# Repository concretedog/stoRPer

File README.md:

# 

stoRPer, a modular adaptable AWD Pico based robot rover

[Check out the youtube video](https://youtu.be/Y8ddx1Og3Xw?feature=shared) with details about the design and the design thinking, at the moment it's probably the best documentation! 

Basic Bill Of Materials, This is just a guide for a basic build as you could build up the PCB in any way you can imagine!

- The PCB, Available on [Tindie](https://www.tindie.com/products/concreted0g/storper/)
- 4* N20 metal gear motors in a gear ratio of your choice rated up to 6V. <br />
- 4* 3D printed motor mount clips to attach the motors (files in the 3D models section or periodically available on the tindie listing as an options)<br />
- 8* 6mm M2 bolts and nuts to attach motor mounts.<br />
- A raspberry pi Pico or Pico W, or equivalent footprint microcontroller board.<br />
- Some N20 compatible wheels (either commercial or home brew/3D printed)<br />
- Some kind of power supply (simplest is a small USB pack, other options are a 14500 or 18650 cell wired into the power input)<br />
- Semi optional, an upper deck to attach power supply too. (Inkscape files for Lasercutting or CNC or heck, cutting out with a saw, are in the Deck Drawing folder, or available lasercut on the Tindie listing)<br />

But that's just a guide, you could use different items or design to the basic PCB/chassis in different ways. <br />

All the KiCad files in the repo were originally made in version 7.xx. 

**Update 28-05-2024**

Added an Addons folder which currently contains 2 new PCB designs. <br />

Bumper can receive an ultrasonic module (HC-SR04) and also have 2 bump switches connected. <br />
The Kludge Deck conforms to the StoRPer main PCB layout with lots of prototyping space and extra holes for mounting stuff! <br />

Bumpers can be added above or below the main PCB with lots of different mount options. Therefore you might need to buy a range of standoffs to accomodate and support your design. If however you have access to a 3D printer there is a FreeCAD file in the 3D models section called STANDOFFS which you can simply adjust the length of a standoff tube that will slot over an M3 bolt. You can make custom lengths to suit your build. 

**Tiny Update 29-06-25**

Added a small hex adaptor part to the 3D models section. I ran a workshop recently and wanted to use more affordable mecanum wheels and found some cheap 48mm mecanum wheels available on places like aliexpress etc. However they have a hexagonal axle mount. After numerous iterations and dialling in the 3D printing I made a super simple slip on adaptor part that sits inside the wheel and slots on snugly to the N20 motor mount. Useful for stoRPer of course, but useful for any N20 motor project.

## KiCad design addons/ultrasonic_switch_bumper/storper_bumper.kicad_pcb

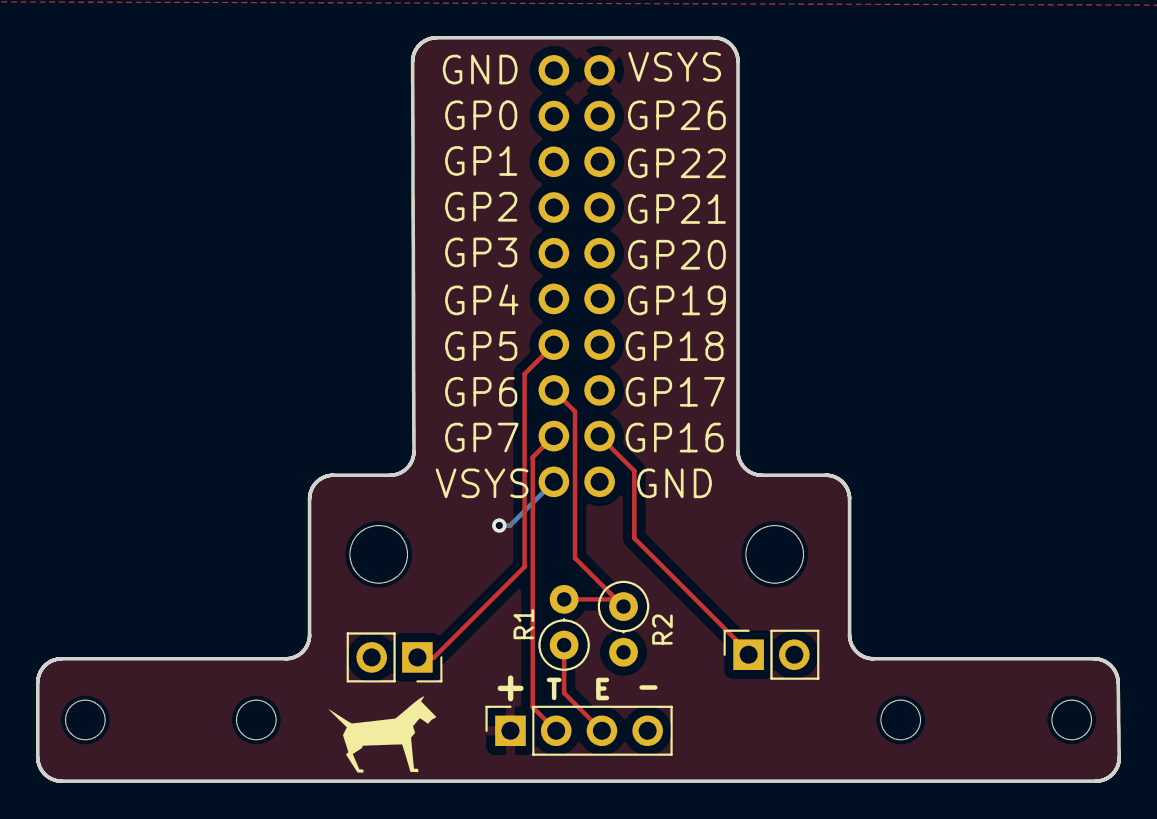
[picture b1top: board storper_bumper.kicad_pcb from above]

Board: 2 copper layers, 60.1 x 41.3 mm, 6 parts (0 on the bottom side), 7 nets.

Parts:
J1: HRS04; PinSocket_1x04_P2.54mm_Vertical
J2, J3: Conn_01x02_Pin; PinSocket_1x02_P2.54mm_Vertical
J12: Conn_02x10_Counter_Clockwise; stoRPer_breakout
R1, R2: R; R_Axial_DIN0207_L6.3mm_D2.5mm_P2.54mm_Vertical

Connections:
/gp5: J2.1, J12.7
/gp6: J12.8, R1.2, R2.1
/gp7: J1.2, J12.9
/gp16: J3.1, J12.12
GND: J1.4, J2.2, J3.2, J12.1, J12.11, R2.2
unnamed: J1.3, R1.1
VSS: J1.1, J12.10, J12.20

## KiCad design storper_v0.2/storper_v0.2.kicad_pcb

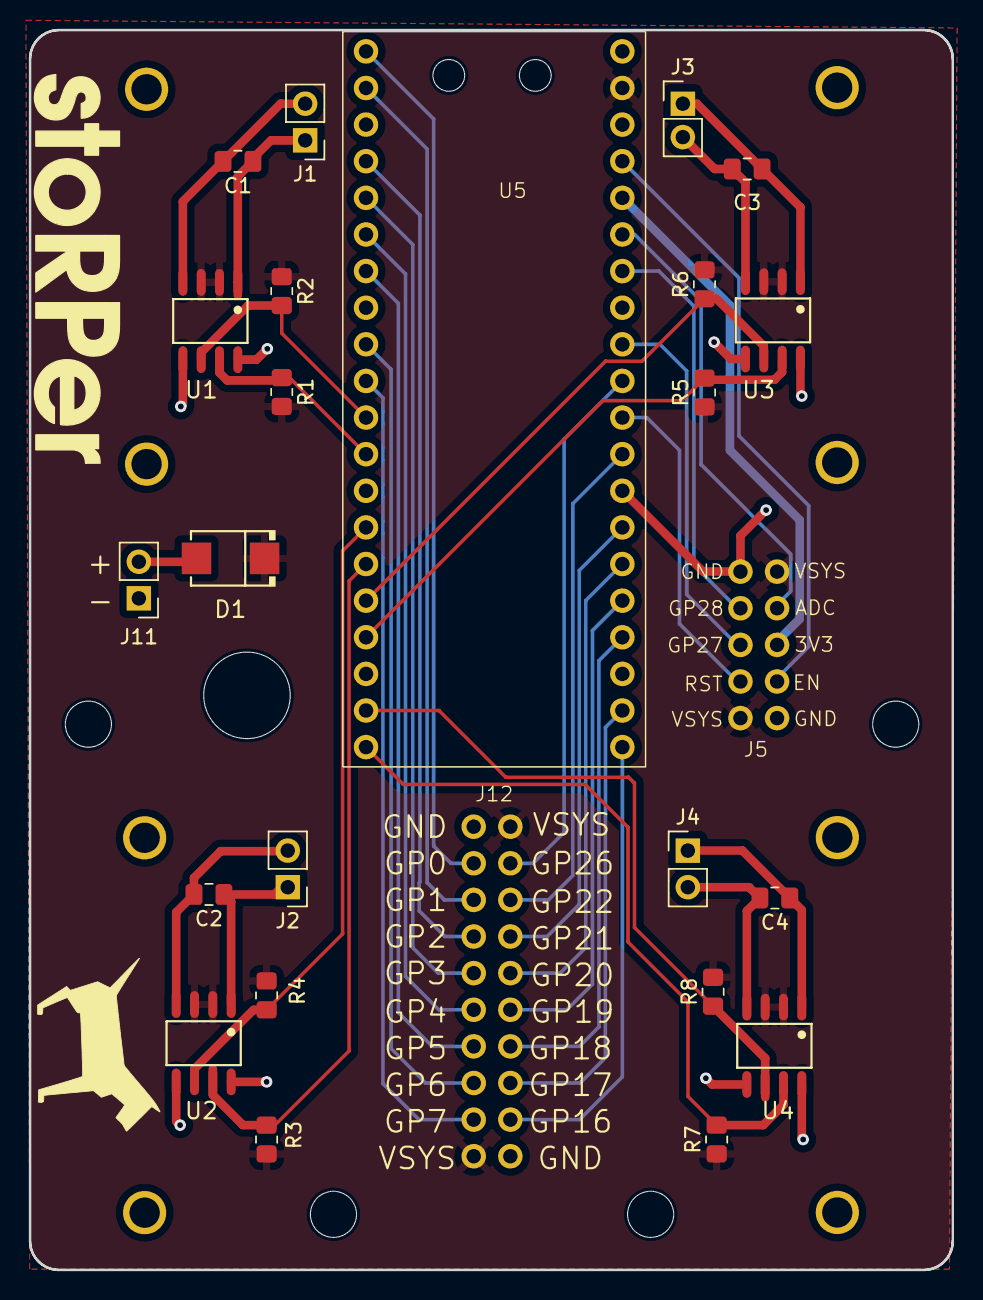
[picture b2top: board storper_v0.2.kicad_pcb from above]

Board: 2 copper layers, 64.0 x 86.0 mm, 25 parts (0 on the bottom side), 41 nets.

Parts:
C1, C2, C3, C4: 0.1uF; C_0805_2012Metric_Pad1.18x1.45mm_HandSolder
D1: D; Diode_Schottky_SMB(DO-214AA)
J1, J2, J3, J4, J11: Conn_01x02_Pin; PinHeader_1x02_P2.54mm_Vertical
J5: Conn_02x05_Counter_Clockwise; StoRPer_small_breakout
J12: Conn_02x10_Counter_Clockwise; stoRPer_breakout
R1, R2, R3, R4, R5, R6, R7, R8: 10k; R_0805_2012Metric_Pad1.20x1.40mm_HandSolder
U1, U2, U3, U4: L9110_Motor_Driver; L9110S_SOP-8_L4.9-W3.9-P1.27-LS6.0-BL
U5: RP_Pico

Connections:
+BATT: D1.2 (A), J11.2
/3V3: J5.8, U5.36 (3V3(out))
/3V3_en: J5.7, U5.37 (3V3_en)
/A1: R2.1, U1.6 (IA), U5.11 (gp8)
/A2: R4.1, U2.6 (IA), U5.14 (gp10)
/A3: R6.1, U3.6 (IA), U5.16 (gp12)
/A4: R8.1, U4.6 (IA), U5.19 (gp14)
/ADC_Vref: J5.9, U5.35 (ADC_vref)
/B1: R1.2, U1.7 (IB), U5.12 (gp9)
/B2: R3.2, U2.7 (IB), U5.15 (gp11)
/B3: R5.2, U3.7 (IB), U5.17 (gp13)
/B4: R7.2, U4.7 (IB), U5.20 (gp15)
/gp0: J12.2, U5.1 (gp0)
/gp1: J12.3, U5.2 (gp1)
/gp2: J12.4, U5.4 (gp2)
/gp3: J12.5, U5.5 (gp3)
/gp4: J12.6, U5.6 (gp4)
/gp5: J12.7, U5.7 (gp5)
/gp6: J12.8, U5.9 (gp6)
/gp7: J12.9, U5.10 (gp7)
/gp16: J12.12, U5.21 (gp16)
/gp17: J12.13, U5.22 (gp17)
/gp18: J12.14, U5.24 (gp18)
/gp19: J12.15, U5.25 (gp19)
/gp20: J12.16, U5.26 (gp20)
/gp21: J12.17, U5.27 (gp21)
/gp22: J12.18, U5.29 (gp22)
/gp26: J12.19, U5.31 (gp26)
/gp27: J5.3, U5.32 (gp27)
/gp28: J5.2, U5.34 (gp28)
/reset: J5.4, U5.30 (RUN)
GND: J5.1, J5.6, J11.1, J12.1, J12.11, U1.5 (GND), U1.8 (GND), U2.5 (GND), U2.8 (GND), U3.5 (GND), U3.8 (GND), U4.5 (GND), U4.8 (GND), U5.3 (GND), U5.8 (GND), U5.13 (GND), U5.18 (GND), U5.23 (GND), U5.28 (GND), U5.33 (GND), U5.38 (GND)
unnamed: C1.1, J1.1, U1.1 (OA)
unnamed: C1.2, J1.2, U1.4 (OB)
unnamed: C2.1, J2.1, U2.1 (OA)
unnamed: C2.2, J2.2, U2.4 (OB)
unnamed: C3.1, J3.1, U3.1 (OA)
unnamed: C3.2, J3.2, U3.4 (OB)
unnamed: C4.1, J4.1, U4.1 (OA)
unnamed: C4.2, J4.2, U4.4 (OB)
VSS: D1.1 (K), J5.5, J5.10, J12.10, J12.20, R1.1, R2.2, R3.1, R4.2, R5.1, R6.2, R7.1, R8.2, U1.2 (VCC), U1.3 (VCC), U2.2 (VCC), U2.3 (VCC), U3.2 (VCC), U3.3 (VCC), U4.2 (VCC), U4.3 (VCC), U5.39 (VSYS)

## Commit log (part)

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2023-11-28 Add files via upload
    Added 3D models
2023-11-28 Add files via upload
    Added KiCad project
2023-11-28 Add files via upload
    Added SVG for add on decks
2023-11-28 Add files via upload
    Added micropython simple examples
2024-03-11 Fix link
2024-03-11 bulleted list
2024-03-11 added a standoff motor mount FreeCAD model
2024-03-17 Seperate schematic files have been combined into one for ease of viewing.
    New file: storper_v0.2/schematics.pdf - pdf version of schematic for reference
    New file: storper_v0.2/storper_v0.2_all.kicad_sch - Combined schematic file
2024-03-18 Added schematic PDF.
2024-05-28 creating bumper folder
2024-05-28 Create folder kludgedeck
2024-05-29 add example for testing an HRCS04 on the bumper
2025-06-29 adding hex wheel adaptor for cheap mecanum wheels
2025-06-29 uploading stl for hex wheel adaptor
2025-06-29 image_budget_mecanums
2025-06-29 Update README.md n20 hex mounts
2025-08-03 Render BOM as a list for slightly better readability
